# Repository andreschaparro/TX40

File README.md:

# PCB TX40

Este repositorio, contiene el diseño en Kicad de una placa para aislar las entradas de un controlador *BRAHMA*.

La entradas, cierran 5V en el PCB, y activan o desactivan 2 reles que se accionaran sobre el controlador original.

Esto es necesario, para que los sensores trabajen con niveles de tension segura.

Originalmente, el controlador tiene una fuente switching no aislada galvanicamente (LNK304) y produce que las entradas del mismo no tengan tensiones de trabajo seguras.

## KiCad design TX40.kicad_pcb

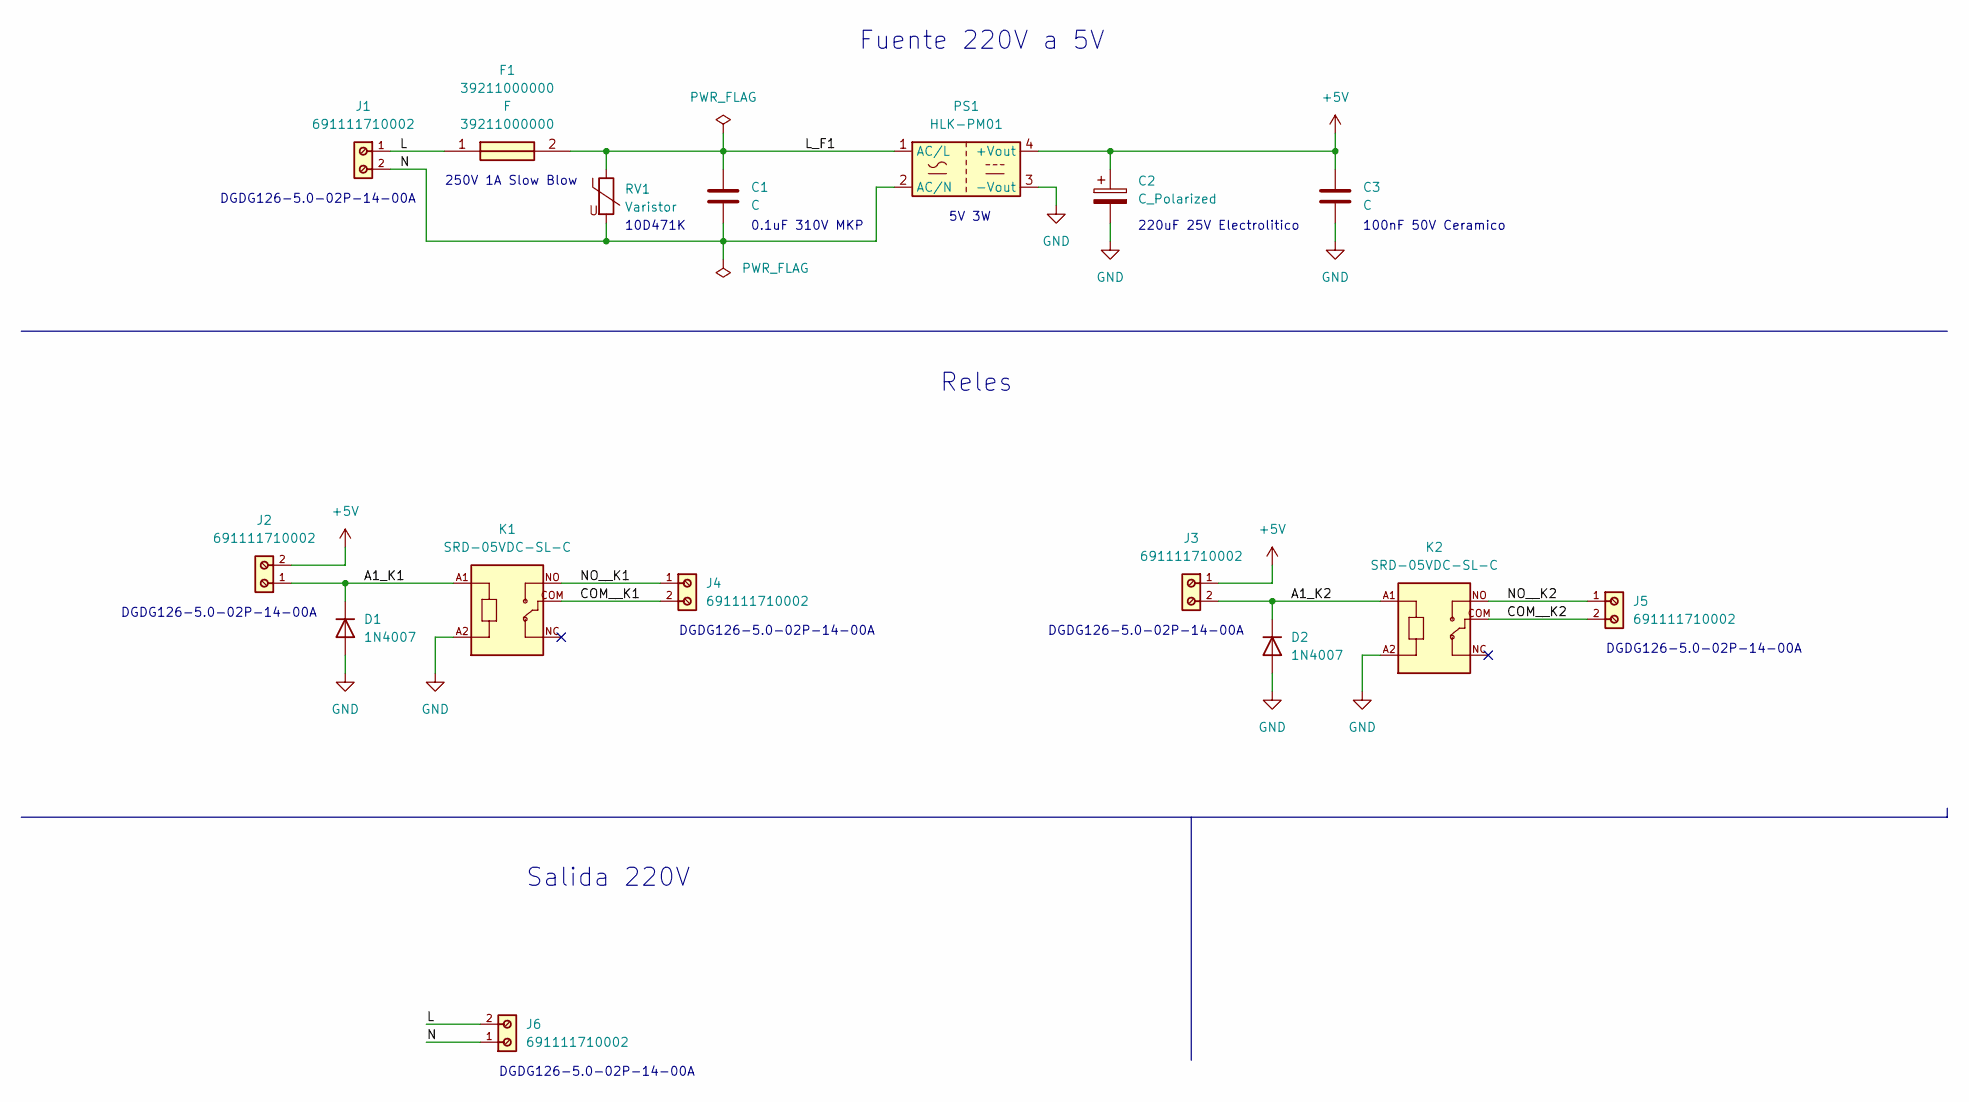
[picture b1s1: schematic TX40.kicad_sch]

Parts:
C1: C; C_Rect_L13.0mm_W6.0mm_P10.00mm_FKS3_FKP3_MKS4
C2: C_Polarized; CP_Radial_D8.0mm_P3.50mm
C3: C; C_Disc_D5.0mm_W2.5mm_P2.50mm
D1, D2: 1N4007; D_DO-41_SOD81_P10.16mm_Horizontal
F1: 39211000000; Manufacturer_Part_Number 39211000000; Mouser Part Number 576-3921100000
J1, J2, J3, J4, J5, J6: 691111710002; PART-NUMBER 691111710002
K1, K2: SRD-05VDC-SL-C; RELAY_SRD-05VDC-SL-C
PS1: HLK-PM01; Converter_ACDC_HiLink_HLK-PMxx
RV1: Varistor; RV_Disc_D12mm_W5.4mm_P7.5mm

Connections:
+5V: C2.1, C3.1, J2.2, J3.1, PS1.4 (+Vout)
/A1_K1: D1.1 (K), J2.1, K1.A1
/A1_K2: D2.1 (K), J3.2, K2.A1
/COM__K1: J4.2, K1.COM
/COM__K2: J5.2, K2.COM
/L: F1.1, J1.1, J6.2
/L_F1: C1.1, F1.2, PS1.1 (AC/L), RV1.1
/N: C1.2, J1.2, J6.1, PS1.2 (AC/N), RV1.2
/NO__K1: J4.1, K1.NO
/NO__K2: J5.1, K2.NO
GND: C2.2, C3.2, D1.2 (A), D2.2 (A), K1.A2, K2.A2, PS1.3 (-Vout)

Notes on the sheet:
Salida 220V
10D471K
250V 1A Slow Blow
220uF 25V Electrolitico
100nF 50V Ceramico
0.1uF 310V MKP
5V 3W
DGDG126-5.0-02P-14-00A
Reles
Fuente 220V a 5V

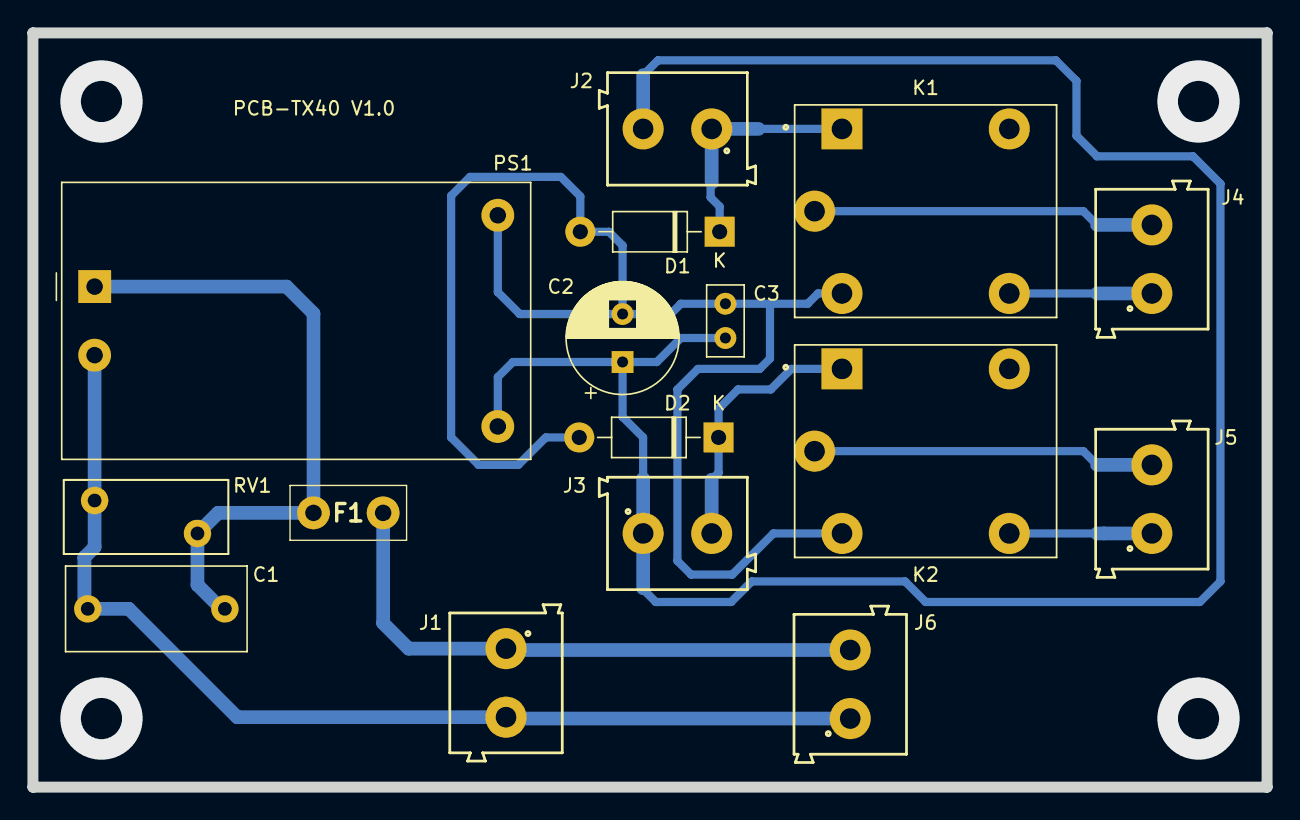
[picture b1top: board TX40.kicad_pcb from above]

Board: 2 copper layers, 90.0 x 55.0 mm, 16 parts (0 on the bottom side), 11 nets.

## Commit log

2024-02-22 Commit Inicial
2024-02-29 Cambio a placa de 55x90
